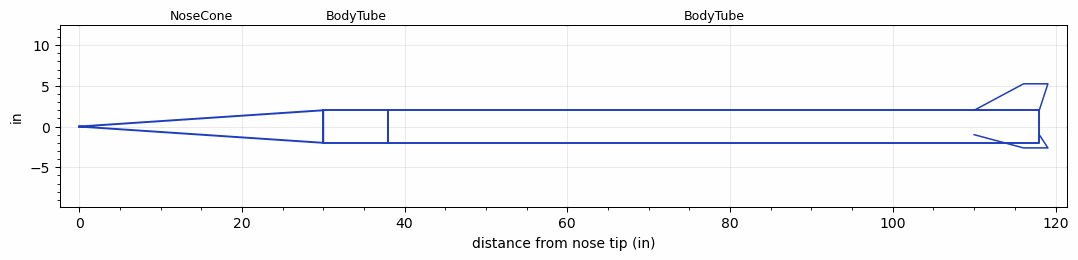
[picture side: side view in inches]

<RASAeroDocument>
 <FileVersion>2</FileVersion>
 <RocketDesign>
  <NoseCone>
   <Length>30</Length>
   <Diameter>4</Diameter>
   <Shape>Conical</Shape>
   <BluntRadius>0.01</BluntRadius>
   <Location>0</Location>
  </NoseCone>
  <BodyTube>
   <Length>8</Length>
   <Diameter>4</Diameter>
   <Location>30</Location>
   <Protuberance>
    <StreamlinedNoBaseDrag>0</StreamlinedNoBaseDrag>
    <StreamlinedWithBaseDrag>0</StreamlinedWithBaseDrag>
    <InclinedPlate1Angle>90</InclinedPlate1Angle>
    <InclinedPlate1FrontalArea>1</InclinedPlate1FrontalArea>
    <InclinedPlate2Angle>90</InclinedPlate2Angle>
    <InclinedPlate2FrontalArea>1</InclinedPlate2FrontalArea>
   </Protuberance>
  </BodyTube>
  <BodyTube>
   <Length>80</Length>
   <Diameter>4</Diameter>
   <RailGuideDiameter>0.5</RailGuideDiameter>
   <RailGuideHeight>0.6</RailGuideHeight>
   <Location>38</Location>
   <Fin>
    <Count>3</Count>
    <Chord>8</Chord>
    <Span>3.25</Span>
    <SweepDistance>6.0622</SweepDistance>
    <TipChord>3</TipChord>
    <Thickness>0.1181</Thickness>
    <LERadius>0.05</LERadius>
    <Location>8</Location>
    <AirfoilSection>Hexagonal</AirfoilSection>
    <FX1>1</FX1>
    <FX3>1</FX3>
   </Fin>
  </BodyTube>
  <Surface>Smooth Paint</Surface>
  <ModifiedBarrowman>False</ModifiedBarrowman>
  <Turbulence>False</Turbulence>
  <UseBooster1>False</UseBooster1>
  <UseBooster2>False</UseBooster2>
 </RocketDesign>
 <LaunchSite>
  <Altitude>0</Altitude>
  <Pressure>0</Pressure>
  <RodAngle>3</RodAngle>
  <RodLength>17</RodLength>
  <Temperature>74</Temperature>
  <WindSpeed>3</WindSpeed>
 </LaunchSite>
 <Recovery>
  <Altitude1>1000</Altitude1>
  <Altitude2>1000</Altitude2>
  <DeviceType1>Parachute</DeviceType1>
  <DeviceType2>Parachute</DeviceType2>
  <Event1>True</Event1>
  <Event2>True</Event2>
  <Size1>12</Size1>
  <Size2>96</Size2>
  <EventType1>Apogee</EventType1>
  <EventType2>Altitude</EventType2>
  <CD1>1</CD1>
  <CD2>1.5</CD2>
 </Recovery>
 <SimulationList>
  <Simulation>
   <SustainerEngine>N5800-CS  (CTI)</SustainerEngine>
   <SustainerLaunchWt>67.6</SustainerLaunchWt>
   <SustainerNozzleDiameter>2.7</SustainerNozzleDiameter>
   <SustainerCG>74.5</SustainerCG>
   <SustainerIgnitionDelay>0</SustainerIgnitionDelay>
   <Booster1SeparationDelay>0</Booster1SeparationDelay>
   <Booster1IgnitionDelay>0</Booster1IgnitionDelay>
   <IncludeBooster1>False</IncludeBooster1>
   <Booster2Delay>0</Booster2Delay>
   <IncludeBooster2>False</IncludeBooster2>
   <TimetoApogee>36.58987</TimetoApogee>
   <MaxAltitude>26976.92</MaxAltitude>
   <MaxVelocity>2147.614</MaxVelocity>
  </Simulation>
 </SimulationList>
</RASAeroDocument>
